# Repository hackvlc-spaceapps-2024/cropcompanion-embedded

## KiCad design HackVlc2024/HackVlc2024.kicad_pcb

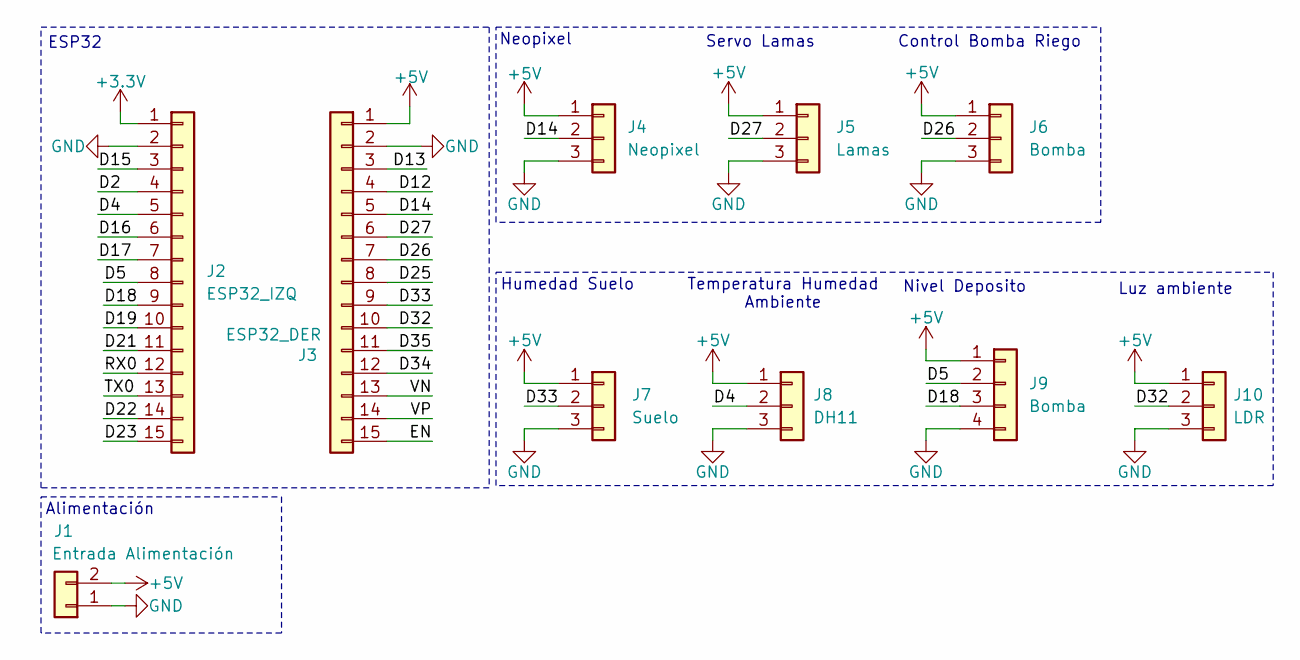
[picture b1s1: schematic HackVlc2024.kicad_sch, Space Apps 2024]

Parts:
J1: Entrada Alimentación; TerminalBlock_Phoenix_MKDS-1,5-2_1x02_P5.00mm_Horizontal
J2: ESP32_IZQ; PinSocket_1x15_P2.54mm_Vertical
J3: ESP32_DER; PinSocket_1x15_P2.54mm_Vertical
J4: Neopixel; JST_XH_B3B-XH-A_1x03_P2.50mm_Vertical
J5: Lamas; JST_XH_B3B-XH-A_1x03_P2.50mm_Vertical
J6: Bomba; JST_XH_B3B-XH-A_1x03_P2.50mm_Vertical
J7: Suelo; JST_XH_B3B-XH-A_1x03_P2.50mm_Vertical
J8: DH11; JST_XH_B3B-XH-A_1x03_P2.50mm_Vertical
J9: Bomba; JST_XH_B4B-XH-A_1x04_P2.50mm_Vertical
J10: LDR; JST_XH_B3B-XH-A_1x03_P2.50mm_Vertical

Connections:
+3.3V: J2.1
+5V: J1.2, J3.1, J4.1, J5.1, J6.1, J7.1, J8.1, J9.1, J10.1
/D2: J2.4
/D4: J2.5, J8.2
/D5: J2.8, J9.2
/D12: J3.4
/D13: J3.3
/D14: J3.5, J4.2
/D15: J2.3
/D16: J2.6
/D17: J2.7
/D18: J2.9, J9.3
/D19: J2.10
/D21: J2.11
/D22: J2.14
/D23: J2.15
/D25: J3.8
/D26: J3.7, J6.2
/D27: J3.6, J5.2
/D32: J3.10, J10.2
/D33: J3.9, J7.2
/D34: J3.12
/D35: J3.11
/EN: J3.15
/RX0: J2.12
/TX0: J2.13
/VN: J3.13
/VP: J3.14
GND: J1.1, J2.2, J3.2, J4.3, J5.3, J6.3, J7.3, J8.3, J9.4, J10.3

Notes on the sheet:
Alimentación
Control Bomba Riego
Temperatura Humedad Ambiente
Neopixel
Nivel Deposito
Servo Lamas
Humedad Suelo
Luz ambiente
ESP32

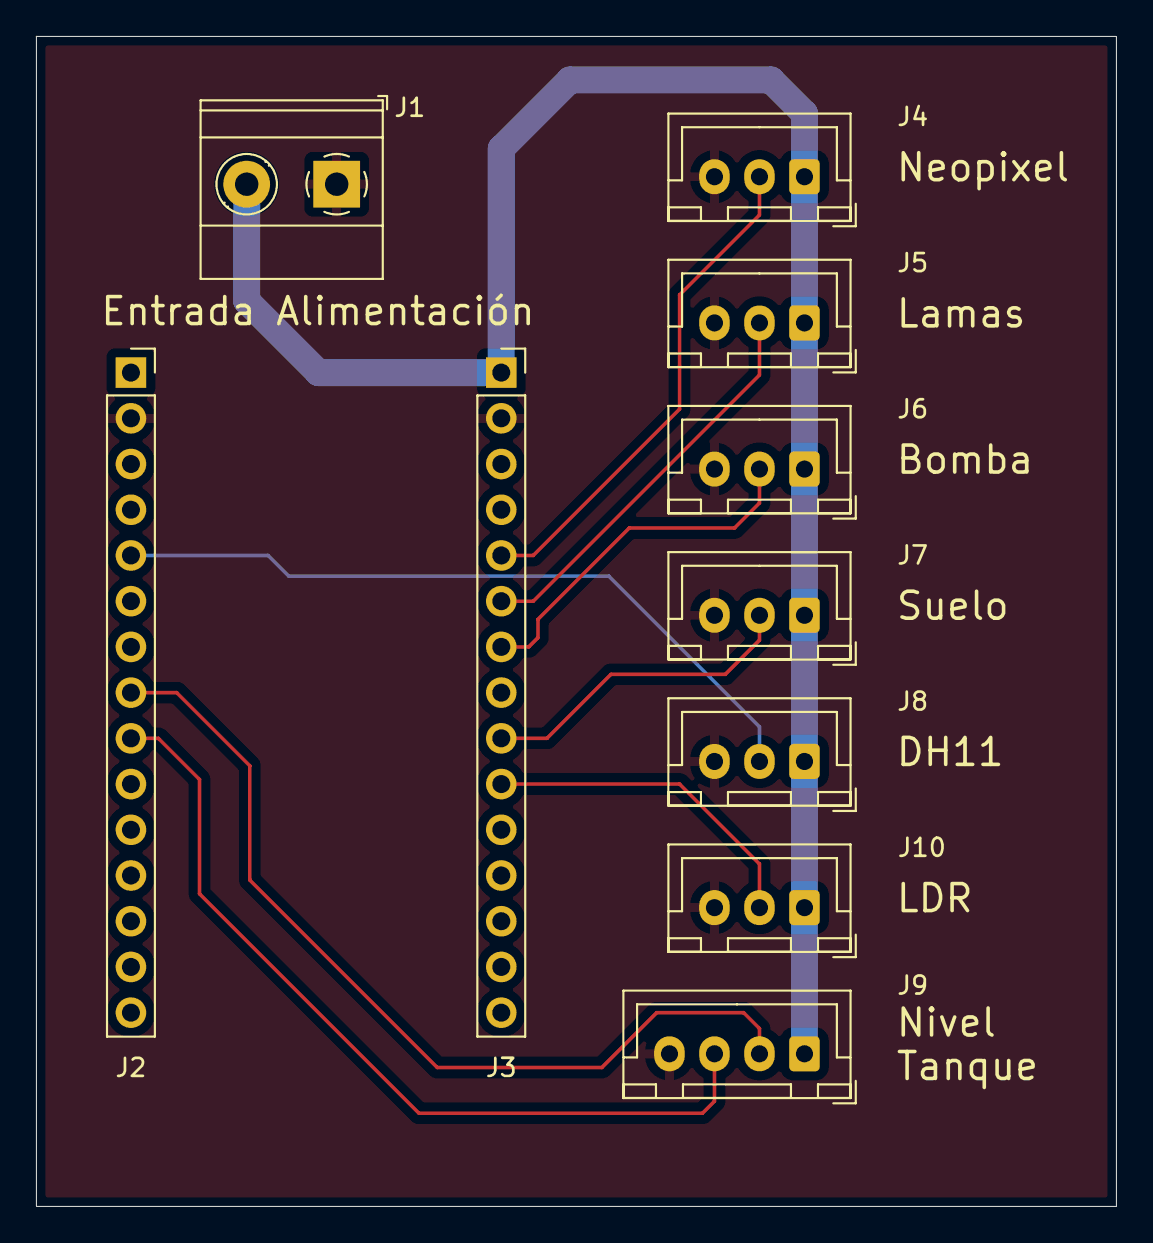
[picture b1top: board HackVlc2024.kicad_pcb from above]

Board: 2 copper layers, 60.0 x 65.0 mm, 10 parts (0 on the bottom side), 10 nets.

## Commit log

2024-10-05 Añadir KICAD
2024-10-05 Casi las 12
2024-10-05 PCB acida
2024-10-05 Serigrafia
2024-10-05 Versión final de hoy por la mañana
2024-10-05 Pin luz a 32
2024-10-05 Pin 4 cambiado a 34
2024-10-05 Versión final de hoy
2024-10-06 D34 vuelve a ser D4
    Por el DH11
